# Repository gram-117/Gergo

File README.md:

# Gergo 
Gram's ergonomic keyboard is based on Klor and Kaly42 keyboards. Uses a 40-key layout, with splay from Klor and the thumb cluster found in Kaly with some small modifications. Firmware is QMK. The graphic found on both the front and back depicts a morning glory flower, a flower that grew in the backyard of my childhood home :)

# Materials needed:
this keyboard requires some level of experience with soldering and requires the following materials in addition to the PCB:

2x Elite-C MCU (atmega32u4)

40x Cherry mx compatible key switches

40x Cherry mx compatible keycaps

2x TRRS jacks (PJ-320A) *

40x 1N4148 Diodes

1x TRRS cable *

(TRS may be used, however, I will get to that later, I would recommend TRRS as that is what I am currently using and it is known to work)

Optional:

40x Kailh hot swap sockets (while not technically needed, it is a nice feature to have. I opted for clear HS sockets)

2x EC11 Rotary Encoder (not required however they have been very fun to play with and I would recommend them)

Rubber/ Silicone bump-ons (allow the PCB to be used bare without any sliding around without a case)

2x key-switch plate (the one pictured is laser cut acrylic so you can still see PCB graphics, 3D printing would work as well but I feel it would take away from the aesthetics

2x reset switch (I am putting this in optional because the Elite-C has an onboard reset switch, and since the controller is exposed you can also short the RST pin. I don't have reset switches on my current build.)

rubber/silicone bump-ons mentioned above:

# Notes:
For my specific build:

I used Gateron beer switches which I have come to love, they are somewhat lighter than holy pandas but still feel amazing. The keycaps were resin printed, however, they came out somewhat consistent. They can be found under KLP-Lame-Keycaps on github, the issues I had were due to printer error the keycap files are very well done and I appreciate them being free to the public. I will likely remake a new set at some point. The plate is 1.5mm clear acrylic, 1.5mm thickness is necessary for this build as the plate is held up by the switches alone so the switches must click into the plate. PCB was ordered from JLC and I had a great experience with them. 

In hindsight, I wish I had used a pro-micro footprint so I could try out Bluetooth and ZMK without having to design a new board, as the PCB is compatible ONLY with the Elite-C as well as I am aware. Having diode clusters looks nice but routing them isn't nice, I am unsure if I will continue to include them in further designs. Originally, I had planned for the two halves to communicate using I2C, which was changed to serial, so pins D0 and D1 can be used for serial communications between the two halves. The current PCB also includes a place for pull-up resistors on the right half but if you plan to build this keyboard in serial (which I would recommend), just ignore them. I had read somewhere that I2C was faster, however, was having trouble with the firmware and decided to switch to serial. At some point I may design a full case which will be added to this repository but for now I recommend adding rubber feet to the bare PCB and potentially adding a plate.

# Future Plans
I am very happy with how this keyboard came out and have been playing around with different keymaps for awhile. In the future, I want to try Kailh low-profile switches and maybe a 38-key layout similar to the totem. Features I have been looking into including in my next project are OLED, some sort of tenting solution, Bluetooth + ZMK, and integrated MCU.

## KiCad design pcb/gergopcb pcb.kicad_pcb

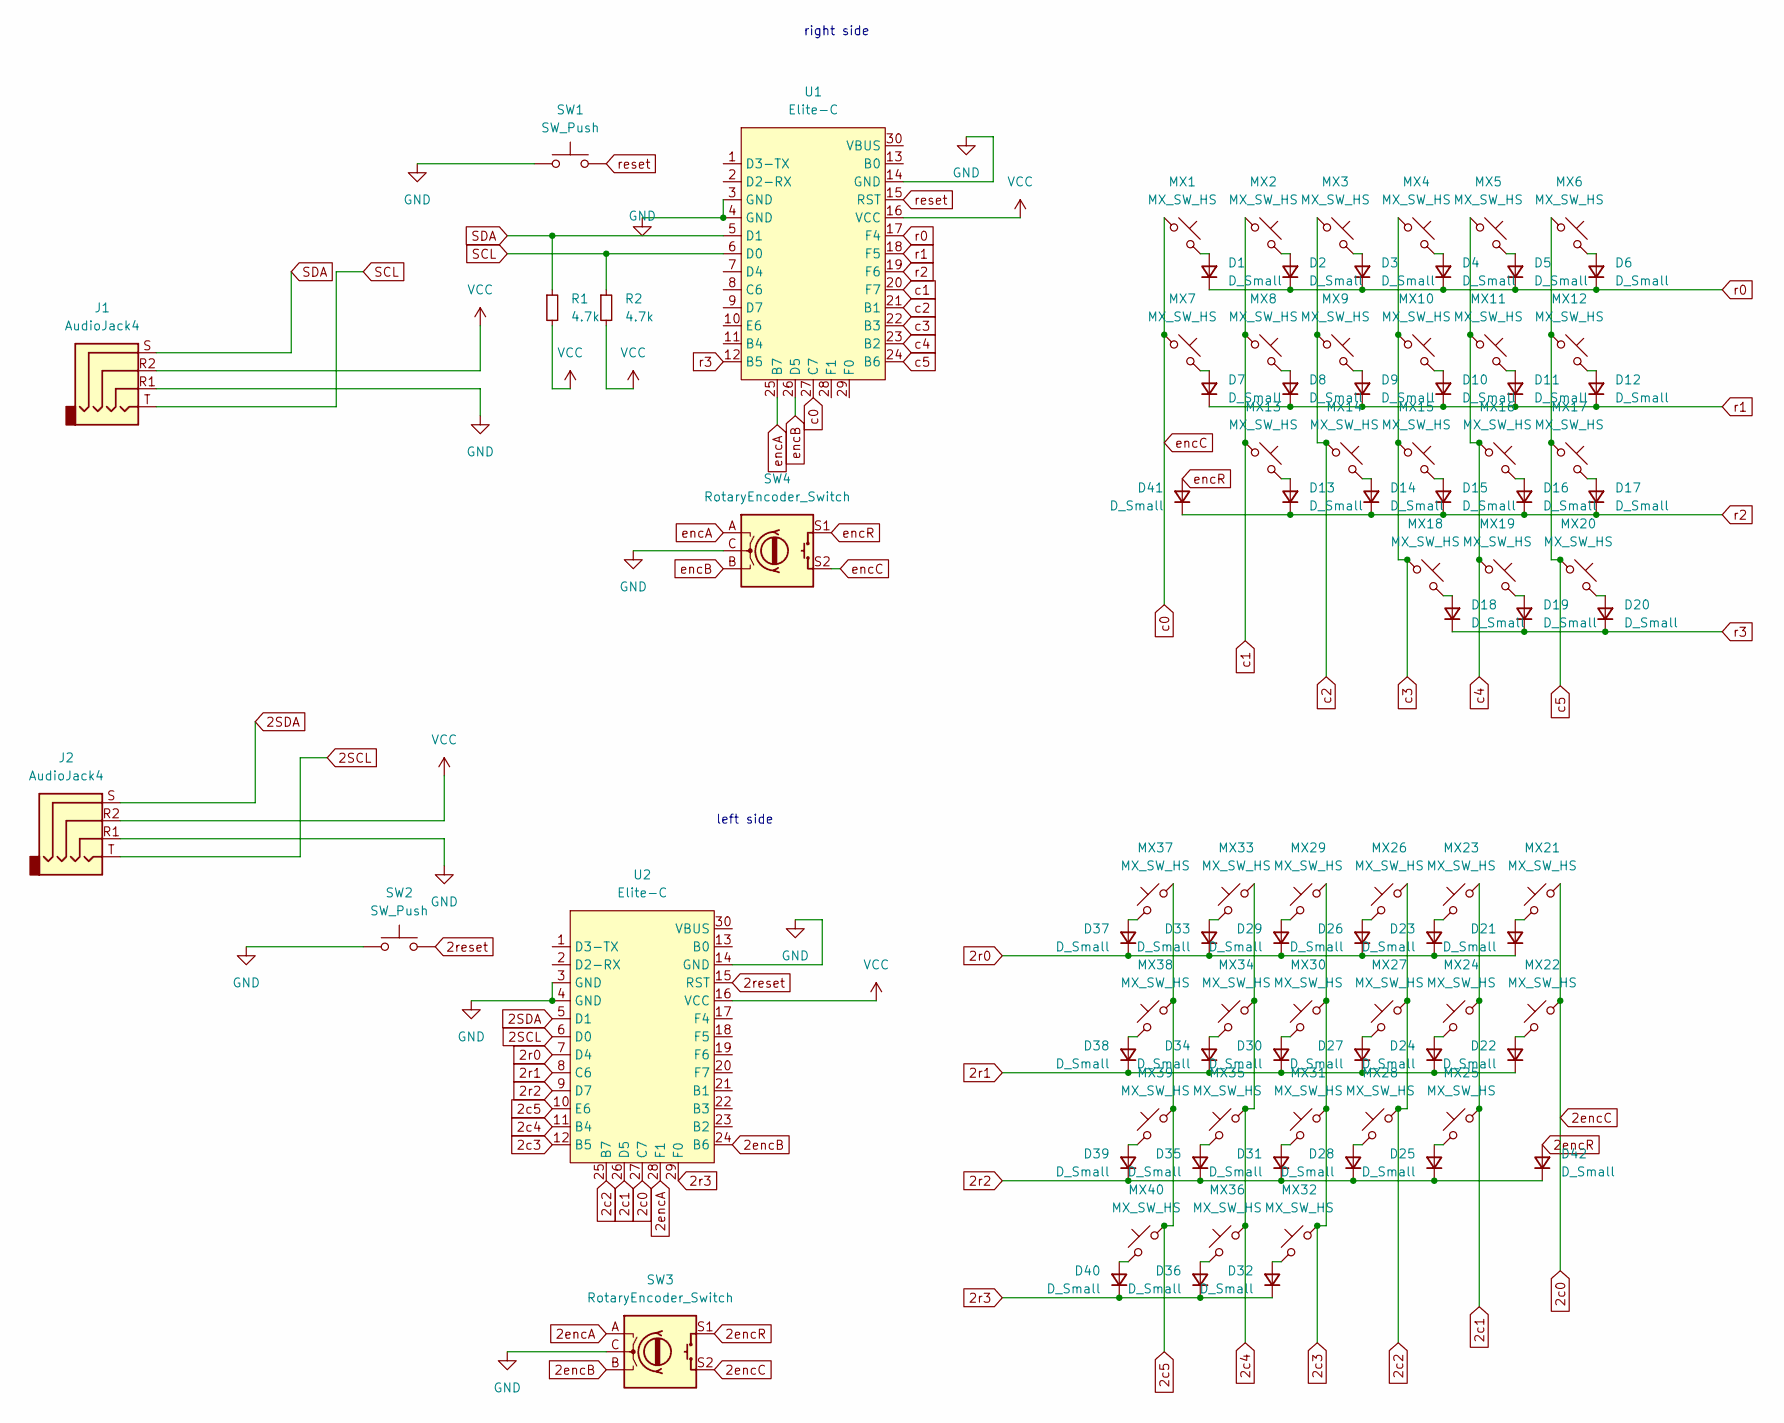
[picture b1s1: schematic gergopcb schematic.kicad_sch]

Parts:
D1, D2, D3, D4, D5, D6, D7, D8, D9, D10, D11, D12, D13, D14, D15, D16, D17, D18, D19, D20, D21, D22, D23, D24, D25, D26, D27, D28, D29, D30, D31, D32, D33, D34, D35, D36, D37, D38, D39, D40, D41, D42: D_Small; D_DO-35_SOD27_P5.08mm_Vertical_AnodeUp
J1, J2: AudioJack4; CON_MJ-4PP-9_Reversible
MX1, MX2, MX3, MX4, MX5, MX6, MX7, MX8, MX9, MX10, MX11, MX12, MX13, MX14, MX15, MX16, MX17, MX18, MX19, MX20, MX21, MX22, MX23, MX24, MX25, MX26, MX27, MX28, MX29, MX30, MX31, MX32, MX33, MX34, MX35, MX36, MX37, MX38, MX39, MX40: MX_SW_HS; SW_MX_HS_CPG151101S11_1u
R1, R2: 4.7k; R_0805_2012Metric_Pad1.20x1.40mm_HandSolder
SW1, SW2: SW_Push; SW_SPST_SKQG_WithStem
SW3, SW4: RotaryEncoder_Switch; ROT_Alps_EC11E-Switch
U1, U2: Elite-C; Elite-C_ACH

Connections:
2SCL: J2.T, U2.6 (D0)
2SDA: J2.S, U2.5 (D1)
2c0: MX21.1, MX22.1, SW3.S2, U2.27 (C7)
2c1: MX23.1, MX24.1, MX25.1, U2.26 (D5)
2c2: MX26.1, MX27.1, MX28.1, U2.25 (B7)
2c3: MX29.1, MX30.1, MX31.1, MX32.1, U2.12 (B5)
2c4: MX33.1, MX34.1, MX35.1, MX36.1, U2.11 (B4)
2c5: MX37.1, MX38.1, MX39.1, MX40.1, U2.10 (E6)
2encA: SW3.A, U2.28 (F1)
2encB: SW3.B, U2.24 (B6)
2encR: D42.2 (A), SW3.S1
2r0: D21.1 (K), D23.1 (K), D26.1 (K), D29.1 (K), D33.1 (K), D37.1 (K), U2.7 (D4)
2r1: D22.1 (K), D24.1 (K), D27.1 (K), D30.1 (K), D34.1 (K), D38.1 (K), U2.8 (C6)
2r2: D25.1 (K), D28.1 (K), D31.1 (K), D35.1 (K), D39.1 (K), D42.1 (K), U2.9 (D7)
2r3: D32.1 (K), D36.1 (K), D40.1 (K), U2.29 (F0)
2reset: SW2.2, U2.15 (RST)
GND: J1.R1, J2.R1, SW1.1, SW2.1, SW3.C, SW4.C, U1.3 (GND), U1.4 (GND), U1.14 (GND), U2.3 (GND), U2.4 (GND), U2.14 (GND)
unnamed: D1.2 (A), MX1.2
unnamed: D2.2 (A), MX2.2
unnamed: D3.2 (A), MX3.2
unnamed: D4.2 (A), MX4.2
unnamed: D5.2 (A), MX5.2
unnamed: D6.2 (A), MX6.2
unnamed: D7.2 (A), MX7.2
unnamed: D8.2 (A), MX8.2
unnamed: D9.2 (A), MX9.2
unnamed: D10.2 (A), MX10.2
unnamed: D11.2 (A), MX11.2
unnamed: D12.2 (A), MX12.2
unnamed: D13.2 (A), MX13.2
unnamed: D14.2 (A), MX14.2
unnamed: D15.2 (A), MX15.2
unnamed: D16.2 (A), MX16.2
unnamed: D17.2 (A), MX17.2
unnamed: D18.2 (A), MX18.2
unnamed: D19.2 (A), MX19.2
unnamed: D20.2 (A), MX20.2
unnamed: D21.2 (A), MX21.2
unnamed: D22.2 (A), MX22.2
unnamed: D23.2 (A), MX23.2
unnamed: D24.2 (A), MX24.2
unnamed: D25.2 (A), MX25.2
unnamed: D26.2 (A), MX26.2
unnamed: D27.2 (A), MX27.2
unnamed: D28.2 (A), MX28.2
unnamed: D29.2 (A), MX29.2
unnamed: D30.2 (A), MX30.2
unnamed: D31.2 (A), MX31.2
unnamed: D32.2 (A), MX32.2
unnamed: D33.2 (A), MX33.2
unnamed: D34.2 (A), MX34.2
unnamed: D35.2 (A), MX35.2
unnamed: D36.2 (A), MX36.2
unnamed: D37.2 (A), MX37.2
unnamed: D38.2 (A), MX38.2
unnamed: D39.2 (A), MX39.2
unnamed: D40.2 (A), MX40.2
SCL: J1.T, R2.1, U1.6 (D0)
SDA: J1.S, R1.1, U1.5 (D1)
VCC: J1.R2, J2.R2, R1.2, R2.2, U1.16 (VCC), U2.16 (VCC)
c0: MX1.1, MX7.1, SW4.S2, U1.27 (C7)
c1: MX2.1, MX8.1, MX13.1, U1.20 (F7)
c2: MX3.1, MX9.1, MX14.1, U1.21 (B1)
c3: MX4.1, MX10.1, MX15.1, MX18.1, U1.22 (B3)
c4: MX5.1, MX11.1, MX16.1, MX19.1, U1.23 (B2)
c5: MX6.1, MX12.1, MX17.1, MX20.1, U1.24 (B6)
encA: SW4.A, U1.25 (B7)
encB: SW4.B, U1.26 (D5)
encR: D41.2 (A), SW4.S1
r0: D1.1 (K), D2.1 (K), D3.1 (K), D4.1 (K), D5.1 (K), D6.1 (K), U1.17 (F4)
r1: D7.1 (K), D8.1 (K), D9.1 (K), D10.1 (K), D11.1 (K), D12.1 (K), U1.18 (F5)
r2: D13.1 (K), D14.1 (K), D15.1 (K), D16.1 (K), D17.1 (K), D41.1 (K), U1.19 (F6)
r3: D18.1 (K), D19.1 (K), D20.1 (K), U1.12 (B5)
reset: SW1.2, U1.15 (RST)

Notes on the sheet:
left side
right side

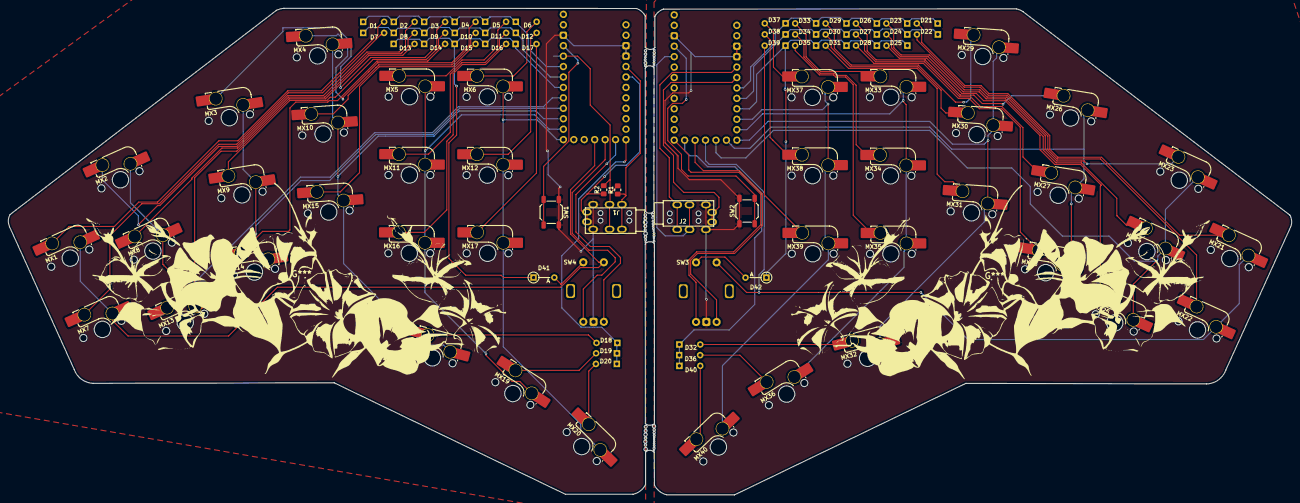
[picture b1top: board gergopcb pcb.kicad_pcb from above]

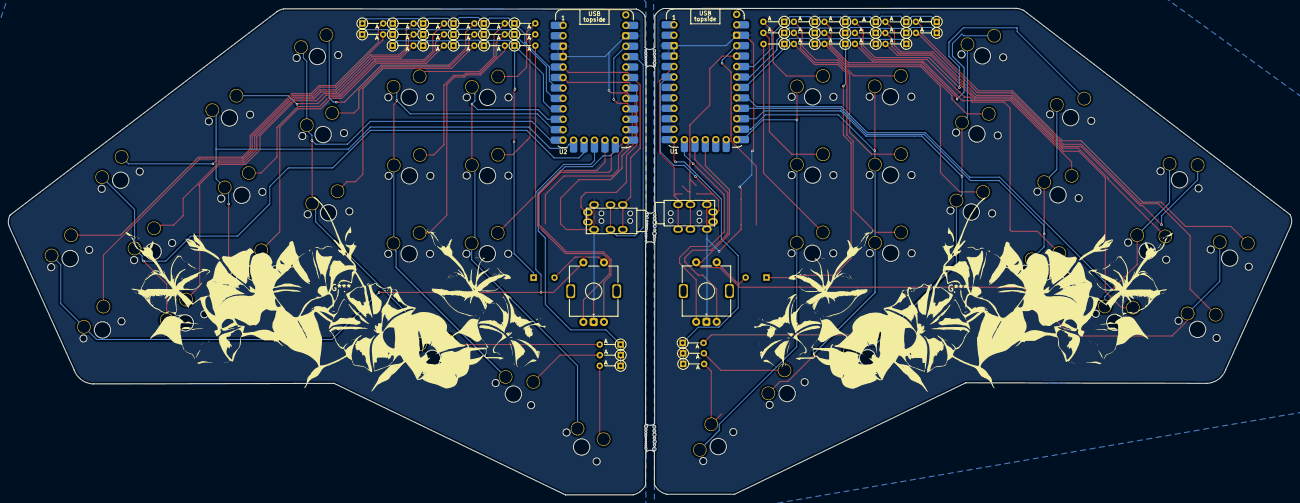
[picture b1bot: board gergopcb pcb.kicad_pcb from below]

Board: 2 copper layers, 312.3 x 118.4 mm, 92 parts (44 on the bottom side), 74 nets.

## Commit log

2024-10-25 Create pcb files
2024-10-25 Create pcb
2024-10-25 Create gerbers
2024-10-25 Create ger
2024-10-25 Create firm
2024-10-25 Create p
